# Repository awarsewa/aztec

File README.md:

# aztec
Bringing a 1976 pinball machine back to life.

[:corn: Wiki](https://github.com/awarsewa/aztec/wiki)

### The machine
Aztec is a Williams® pinball machine for 4 players. Check it out on the [Internet Pinball Machine Database](https://www.ipdb.org/machine.cgi?gid=119). There is also a [solid state version](https://www.ipdb.org/machine.cgi?gid=4828) of the same machine. Mine is from the electromechanical series -- and this is where the fun starts. Of course it wasn't functional. The entire cabinet had been completely gutted, with only a few tilt mechanisms left dangling about. However, the playfield and the backbox were still mostly intact. Repairing it seemed tough, but since it's cool to have your own pinball machine, I decided to give it a shot.

### The project
It would have been rather expensive and difficult to get original spare parts for, or replicas of, all the missing components. So why not replace aztec's brain with a microcontroller? The looks and feel of the machine would still be the same. Only what's under the hood would be slightly more modern. Maybe this is a sacrilege for real pinball lovers... I have a feeling it is. Like an inverse Frankenstein - pretty on the outside. But I already did it, so there's no way back and no repentance. If you want to know how I've done it, check out the [:corn: repository wiki](https://github.com/awarsewa/aztec/wiki).

### What's in this repository?
The source code running on the microcontroller and the PCB schematics. Basically everything you need to do something similar. 

### Getting involved
In case you have questions or suggestions, need support or simply want to get in touch, feel free to [send me a message](mailto:alexander.warsewa@posteo.net?subject=[Aztec]).

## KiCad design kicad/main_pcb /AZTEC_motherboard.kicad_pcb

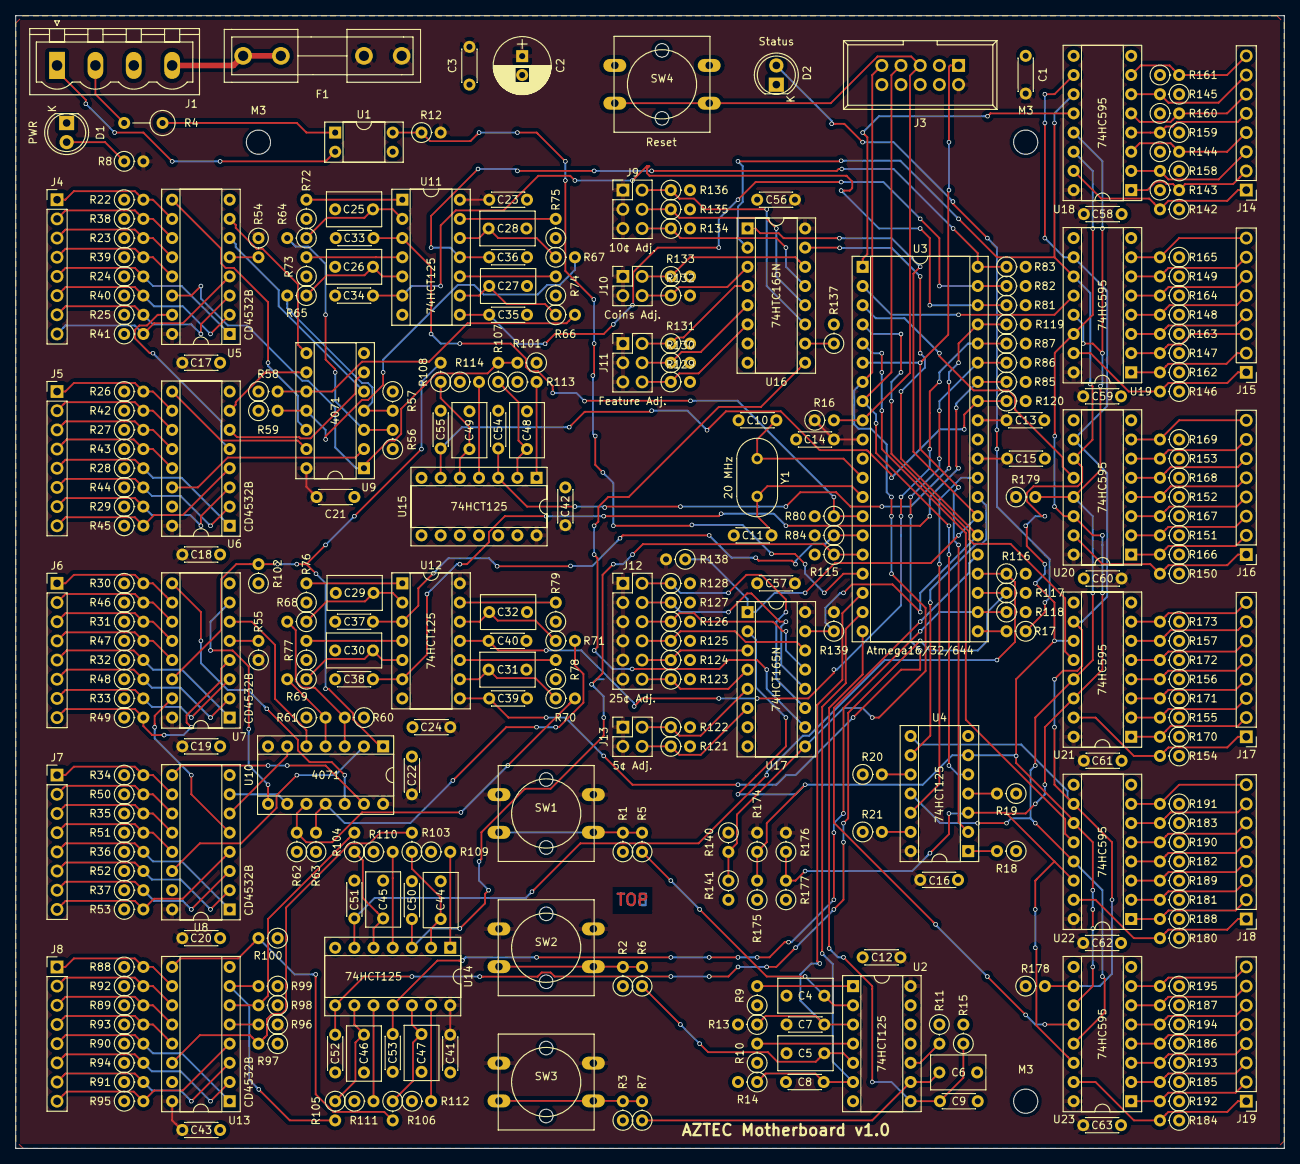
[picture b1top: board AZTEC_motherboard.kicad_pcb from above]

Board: 2 copper layers, 168.0 x 150.0 mm, 310 parts (0 on the bottom side), 227 nets.

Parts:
C1, C3, C7, C8, C9, C12, C13, C14, C15, C16, C17, C18, C19, C20, C21, C22, C23, C24, C33, C34, C35, C36, C37, C38, C39, C40, C41, C42, C43, C50, C51, C52, C53, C54, C55, C56, C57, C58, C59, C60, C61, C62, C63: 100n; C_Disc_D4.3mm_W1.9mm_P5.00mm
C2: 1u; CP_Radial_D7.5mm_P2.50mm
C4, C5, C6, C25, C26, C27, C28, C29, C30, C31, C32, C44, C45, C46, C47, C48, C49: 1µ; C_Rect_L7.2mm_W4.5mm_P5.00mm_FKS2_FKP2_MKS2_MKP2
C10, C11: 22p; C_Disc_D4.3mm_W1.9mm_P5.00mm
D1: PWR; LED-5MM
D2: STATUS; LED-5MM
F1: Fuse; Fuseholder5x20_horiz_open_inline_Type-I
J1: Conn_01x04_Female; PhoenixContact_MSTBVA-G_04x5.08mm_Vertical
J3: ISP; IDC_Header_Straight_10pins
J4: Inputs_1; Pin_Header_Straight_1x08_Pitch2.54mm
J5: Inputs_2; Pin_Header_Straight_1x08_Pitch2.54mm
J6: Inputs_3; Pin_Header_Straight_1x08_Pitch2.54mm
J7: Inputs_4; Pin_Header_Straight_1x08_Pitch2.54mm
J8: Inputs_5; Pin_Header_Straight_1x08_Pitch2.54mm
J9: 10¢ Adjust; Pin_Header_Straight_2x03_Pitch2.54mm
J10: 2 coins - 3 plays; Pin_Header_Straight_2x02_Pitch2.54mm
J11: Feature Adjust; Pin_Header_Straight_2x03_Pitch2.54mm
J12: 25¢ Adjust; Pin_Header_Straight_2x06_Pitch2.54mm
J13: 5¢ Adjust; Pin_Header_Straight_2x02_Pitch2.54mm
J14: Outputs_1; Pin_Header_Straight_1x08_Pitch2.54mm
J15: Outputs_2; Pin_Header_Straight_1x08_Pitch2.54mm
J16: Outputs_3; Pin_Header_Straight_1x08_Pitch2.54mm
J17: Outputs_4; Pin_Header_Straight_1x08_Pitch2.54mm
J18: Outputs_5; Pin_Header_Straight_1x08_Pitch2.54mm
J19: Outputs_6; Pin_Header_Straight_1x08_Pitch2.54mm
M3, M3#2, M3#3: MountingHole_3.2mm_M3
R1, R2, R3, R9, R10, R11, R12, R13, R14, R15, R16, R18, R19, R20, R21, R22, R23, R24, R25, R26, R27, R28, R29, R30, R31, R32, R33, R34, R35, R36, R37, R38, R39, R40, R41, R42, R43, R44, R45, R46, R47, R48, R49, R50, R51, R52, R53, R54, R55, R56, R57, R58, R59, R60, R61, R62, R63, R72, R73, R74, R75, R76, R77, R78, R79, R80, R81, R82, R83, R84, R85, R86, R87, R88, R89, R90, R91, R92, R93, R94, R95, R96, R97, R98, R99, R100, R101, R102, R109, R110, R111, R112, R113, R114, R115, R116, R117, R118, R119, R120, R121, R122, R123, R124, R125, R126, R127, R128, R129, R130, R131, R132, R133, R134, R135, R136, R137, R138, R139, R140, R141, R142, R143, R144, R145, R146, R147, R148, R149, R150, R151, R152, R153, R154, R155, R156, R157, R158, R159, R160, R161, R162, R163, R164, R165, R166, R167, R168, R169, R170, R171, R172, R173, R174, R175, R176, R177, R178, R179, R180, R181, R182, R183, R184, R185, R186, R187, R188, R189, R190, R191, R192, R193, R194, R195: 10k; R_Axial_DIN0207_L6.3mm_D2.5mm_P2.54mm_Vertical
R4: 2k2; R_Axial_DIN0309_L9.0mm_D3.2mm_P5.08mm_Vertical
R5, R6, R7, R64, R65, R66, R67, R68, R69, R70, R71, R103, R104, R105, R106, R107, R108: 22k; R_Axial_DIN0207_L6.3mm_D2.5mm_P2.54mm_Vertical
R8, R17: 100R; R_Axial_DIN0207_L6.3mm_D2.5mm_P2.54mm_Vertical
SW1, SW2, SW3, SW4: Reset; SW_PUSH-AZTEC
U1: SFH620A; DIP-4_W7.62mm_Socket
U2, U4, U11, U12, U14, U15: 74HCT125; DIP-14_W7.62mm_Socket
U3: ATMEGA16/32/644; DIP-40_W15.24mm_Socket
U5, U6, U7, U8, U13: CD4532B; DIP-16_W7.62mm_Socket
U9, U10: 4071; DIP-14_W7.62mm_Socket
U16, U17: 74HCT165N; DIP-16_W7.62mm_Socket
U18, U19, U20, U21, U22, U23: 74HC595; DIP-16_W7.62mm_Socket
Y1: 20 MHz; Resonator-2pin_w10.0mm_h5.0mm

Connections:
/AC_zero_crossing: R12.1, U1.4, U3.17
/Adjusts/CP: R174.1, R175.2, U4.6, U16.2, U17.2, U18.11, U19.11, U20.11, U21.11, U22.11, U23.11
/Adjusts/~CE: R139.1, U3.26, U16.15, U17.15
/Adjusts/~PL: R138.1, U3.27, U16.1, U17.1
/Button1: C7.2, R13.1, U2.3, U3.18
/Button2: C8.2, R14.1, U2.6, U3.19
/Button3: C9.2, R15.1, U2.8, U3.20
/Inputs/GS1: C33.2, R80.1, U3.14, U11.3
/Inputs/GS2: C37.2, R84.1, U3.15, U12.3
/Inputs/GS3: C50.2, R115.1, U3.16, U14.3
/Inputs/Q10: C36.2, R83.1, U3.40, U11.11
/Inputs/Q11: C35.2, R82.1, U3.39, U11.8
/Inputs/Q12: C34.2, R81.1, U3.38, U11.6
/Inputs/Q13: C54.2, R119.1, U3.37, U15.3
/Inputs/Q20: C40.2, R87.1, U3.36, U12.11
/Inputs/Q21: C39.2, R86.1, U3.35, U12.8
/Inputs/Q22: C38.2, R85.1, U3.34, U12.6
/Inputs/Q23: C55.2, R120.1, U3.33, U15.6
/Inputs/Q30: C53.2, R118.1, U3.22, U14.11
/Inputs/Q31: C52.2, R117.1, U3.23, U14.8
/Inputs/Q32: C51.2, R116.1, U3.24, U14.6
/MISO: J3.9, R140.2, R141.1, U3.7, U17.9
/MOSI: J3.1, U3.6, U4.2
/Outputs/MOSI_buf: R176.1, R177.2, U4.3, U18.14, U19.14, U20.14, U21.14, U22.14, U23.14
/Outputs/RCK1: U3.1, U18.12
/Outputs/RCK2: U3.2, U19.12
/Outputs/RCK3: U3.3, U20.12
/Outputs/RCK4: U3.4, U21.12
/Outputs/RCK5: U3.5, U22.12
/Outputs/RCK6: U3.25, U23.12
/Outputs/~OE_buf: R179.2, U4.11, U18.13, U19.13, U20.13, U21.13, U22.13, U23.13
/Outputs/~SCL_buf: R178.2, U4.8, U18.10, U19.10, U20.10, U21.10, U22.10, U23.10
/SCK: J3.7, U3.8, U4.5
/~OE: U3.29, U4.12
/~RESET: J3.5, R16.2, SW4.2, SW4.4, U3.9
/~SCL: U3.28, U4.9
GND: C1.1, C2.2, C3.1, C4.1, C5.1, C6.1, C7.1, C8.1, C9.1, C10.2, C11.2, C12.2, C13.1, C14.1, C15.2, C16.2, C17.1, C18.1, C19.1, C20.1, C21.1, C22.1, C23.2, C24.2, C25.1, C26.1, C27.1, C28.1, C29.1, C30.1, C31.1, C32.1, C33.1, C34.1, C35.1, C36.1, C37.1, C38.1, C39.1, C40.1, C41.2, C42.2, C43.1, C44.1, C45.1, C46.1, C47.1, C48.1, C49.1, C50.1, C51.1, C52.1, C53.1, C54.1, C55.1, C56.1, C57.1, C58.2, C59.2, C60.2, C61.2, C62.2, C63.2, D1.1, D2.1, J1.3, J3.4, J3.6, J3.8, J3.10, R1.1, R2.1, R3.1, R9.1, R10.1, R11.1, R13.2, R14.2, R15.2, R18.1, R19.1, R20.1, R21.1, R22.1, R23.1, R24.1, R25.1, R26.1, R27.1, R28.1, R29.1, R30.1, R31.1, R32.1, R33.1, R34.1, R35.1, R36.1, R37.1, R38.1, R39.1, R40.1, R41.1, R42.1, R43.1, R44.1, R45.1, R46.1, R47.1, R48.1, R49.1, R50.1, R51.1, R52.1, R53.1, R56.1, R57.1, R58.1, R59.1, R60.1, R61.1, R62.1, R63.1, R72.1, R73.1, R74.1, R75.1, R76.1, R77.1, R78.1, R79.1, R80.2, R81.2, R82.2, R83.2, R84.2, R85.2, R86.2, R87.2, R88.1, R89.1, R90.1, R91.1, R92.1, R93.1, R94.1, R95.1, R97.1, R98.1, R99.1, R100.1, R101.1, R102.1, R109.1, R110.1, R111.1, R112.1, R113.1, R114.1, R115.2, R116.2, R117.2, R118.2, R119.2, R120.2, R121.2, R122.2, R123.2, R124.2, R125.2, R126.2, R127.2, R128.2, R129.2, R130.2, R131.2, R132.2, R133.2, R134.2, R135.2, R136.2, R137.2, R141.2, R142.1, R143.1, R144.1, R145.1, R146.1, R147.1, R148.1, R149.1, R150.1, R151.1, R152.1, R153.1, R154.1, R155.1, R156.1, R157.1, R158.1, R159.1, R160.1, R161.1, R162.1, R163.1, R164.1, R165.1, R166.1, R167.1, R168.1, R169.1, R170.1, R171.1, R172.1, R173.1, R175.1, R177.1, R180.1, R181.1, R182.1, R183.1, R184.1, R185.1, R186.1, R187.1, R188.1, R189.1, R190.1, R191.1, R192.1, R193.1, R194.1, R195.1, SW4.1, SW4.3, U1.3, U2.7, U3.11, U3.31, U4.7, U5.8, U6.8, U7.8, U8.8, U9.7, U10.7, U11.7, U12.7, U13.8, U14.7, U15.7, U16.8, U17.8, U18.8, U19.8, U20.8, U21.8, U22.8, U23.8
unnamed: C4.2, R5.1, U2.2
unnamed: C5.2, R6.1, U2.5
unnamed: C6.2, R7.1, U2.9
unnamed: C10.1, U3.12, Y1.1
unnamed: C11.1, U3.13, Y1.2
unnamed: C25.2, R64.1, U11.2
unnamed: C26.2, R65.1, U11.5
unnamed: C27.2, R66.1, U11.9
unnamed: C28.2, R67.1, U11.12
unnamed: C29.2, R68.1, U12.2
unnamed: C30.2, R69.1, U12.5
unnamed: C31.2, R70.1, U12.9
unnamed: C32.2, R71.1, U12.12
unnamed: C44.2, R103.1, U14.2
unnamed: C45.2, R104.1, U14.5
unnamed: C46.2, R105.1, U14.9
unnamed: C47.2, R106.1, U14.12
unnamed: C48.2, R107.1, U15.2
unnamed: C49.2, R108.1, U15.5
unnamed: D1.2, R8.1
unnamed: D2.2, R17.1
unnamed: F1.2, J1.4
unnamed: J1.1, U1.2
unnamed: J1.2, R4.2
unnamed: J4.1, R22.2, U5.10
unnamed: J4.2, R38.2, U5.11
unnamed: J4.3, R23.2, U5.12
unnamed: J4.4, R39.2, U5.13
unnamed: J4.5, R24.2, U5.1
unnamed: J4.6, R40.2, U5.2
unnamed: J4.7, R25.2, U5.3
unnamed: J4.8, R41.2, U5.4
unnamed: J5.1, R26.2, U6.10
unnamed: J5.2, R42.2, U6.11
unnamed: J5.3, R27.2, U6.12
unnamed: J5.4, R43.2, U6.13
unnamed: J5.5, R28.2, U6.1
unnamed: J5.6, R44.2, U6.2
unnamed: J5.7, R29.2, U6.3
unnamed: J5.8, R45.2, U6.4
unnamed: J6.1, R30.2, U7.10
unnamed: J6.2, R46.2, U7.11
unnamed: J6.3, R31.2, U7.12
unnamed: J6.4, R47.2, U7.13
unnamed: J6.5, R32.2, U7.1
unnamed: J6.6, R48.2, U7.2
unnamed: J6.7, R33.2, U7.3
unnamed: J6.8, R49.2, U7.4
unnamed: J7.1, R34.2, U8.10
unnamed: J7.2, R50.2, U8.11
unnamed: J7.3, R35.2, U8.12
unnamed: J7.4, R51.2, U8.13
unnamed: J7.5, R36.2, U8.1
unnamed: J7.6, R52.2, U8.2
unnamed: J7.7, R37.2, U8.3
unnamed: J7.8, R53.2, U8.4
unnamed: J8.1, R88.2, U13.10
unnamed: J8.2, R92.2, U13.11
unnamed: J8.3, R89.2, U13.12
unnamed: J8.4, R93.2, U13.13
unnamed: J8.5, R90.2, U13.1
unnamed: J8.6, R94.2, U13.2
unnamed: J8.7, R91.2, U13.3
unnamed: J8.8, R95.2, U13.4
unnamed: J9.2, R136.1, U16.11
unnamed: J9.4, R135.1, U16.12
unnamed: J9.6, R134.1, U16.13
unnamed: J10.2, R133.1, U16.14
unnamed: J10.4, R132.1, U16.3
unnamed: J11.2, R131.1, U16.4
unnamed: J11.4, R130.1, U16.5
unnamed: J11.6, R129.1, U16.6
unnamed: J12.2, R128.1, U17.11
unnamed: J12.4, R127.1, U17.12
unnamed: J12.6, R126.1, U17.13
unnamed: J12.8, R125.1, U17.14
unnamed: J12.10, R124.1, U17.3
unnamed: J12.12, R123.1, U17.4
unnamed: J13.2, R122.1, U17.5
unnamed: J13.4, R121.1, U17.6
unnamed: J14.1, R142.2, U18.15
unnamed: J14.2, R158.2, U18.1
unnamed: J14.3, R143.2, U18.2
unnamed: J14.4, R159.2, U18.3
unnamed: J14.5, R144.2, U18.4
unnamed: J14.6, R160.2, U18.5
unnamed: J14.7, R145.2, U18.6
unnamed: J14.8, R161.2, U18.7
unnamed: J15.1, R146.2, U19.15
unnamed: J15.2, R162.2, U19.1
unnamed: J15.3, R147.2, U19.2
unnamed: J15.4, R163.2, U19.3
unnamed: J15.5, R148.2, U19.4
unnamed: J15.6, R164.2, U19.5
unnamed: J15.7, R149.2, U19.6
unnamed: J15.8, R165.2, U19.7
unnamed: J16.1, R150.2, U20.15
unnamed: J16.2, R166.2, U20.1
unnamed: J16.3, R151.2, U20.2
unnamed: J16.4, R167.2, U20.3
unnamed: J16.5, R152.2, U20.4
unnamed: J16.6, R168.2, U20.5
unnamed: J16.7, R153.2, U20.6
unnamed: J16.8, R169.2, U20.7
unnamed: J17.1, R154.2, U21.15
unnamed: J17.2, R170.2, U21.1
unnamed: J17.3, R155.2, U21.2
unnamed: J17.4, R171.2, U21.3
unnamed: J17.5, R156.2, U21.4
unnamed: J17.6, R172.2, U21.5
unnamed: J17.7, R157.2, U21.6
unnamed: J17.8, R173.2, U21.7
unnamed: J18.1, R180.2, U22.15
unnamed: J18.2, R188.2, U22.1
unnamed: J18.3, R181.2, U22.2
unnamed: J18.4, R189.2, U22.3
unnamed: J18.5, R182.2, U22.4
unnamed: J18.6, R190.2, U22.5
unnamed: J18.7, R183.2, U22.6
unnamed: J18.8, R191.2, U22.7
unnamed: J19.1, R184.2, U23.15
unnamed: J19.2, R192.2, U23.1
unnamed: J19.3, R185.2, U23.2
unnamed: J19.4, R193.2, U23.3
unnamed: J19.5, R186.2, U23.4
unnamed: J19.6, R194.2, U23.5
unnamed: J19.7, R187.2, U23.6
unnamed: J19.8, R195.2, U23.7
unnamed: R1.2, R5.2, SW1.2, SW1.4
unnamed: R2.2, R6.2, SW2.2, SW2.4
unnamed: R3.2, R7.2, SW3.2, SW3.4
unnamed: R4.1, U1.1
unnamed: R9.2, U2.1
unnamed: R10.2, U2.4
unnamed: R11.2, U2.10
unnamed: R17.2, U3.21
unnamed: R18.2, U4.1
unnamed: R19.2, U4.4
unnamed: R20.2, U4.10
unnamed: R21.2, U4.13
unnamed: R54.2, U5.5
unnamed: R55.2, U7.5
unnamed: R56.2, R64.2, U9.3
unnamed: R57.2, R65.2, U9.4
unnamed: R58.2, R66.2, U9.10
unnamed: R59.2, R67.2, U9.11
unnamed: R60.2, R68.2, U10.3
unnamed: R61.2, R69.2, U10.4
unnamed: R62.2, R70.2, U10.10
unnamed: R63.2, R71.2, U10.11
unnamed: R72.2, U11.1
unnamed: R73.2, U11.4
unnamed: R74.2, U11.10
unnamed: R75.2, U11.13
unnamed: R76.2, U12.1
unnamed: R77.2, U12.4
unnamed: R78.2, U12.10
unnamed: R79.2, U12.13
unnamed: R96.2, U13.5
unnamed: R100.2, R106.2, U13.9
unnamed: R101.2, R107.2, U5.14, U9.1
unnamed: R102.2, R108.2, U7.14, U10.1
unnamed: R97.2, R103.2, U13.14
unnamed: R98.2, R104.2, U13.6
unnamed: R99.2, R105.2, U13.7
unnamed: R109.2, U14.1
unnamed: R110.2, U14.4
unnamed: R111.2, U14.10
unnamed: R112.2, U14.13
unnamed: R113.2, U15.1
unnamed: R114.2, U15.4
unnamed: R137.1, U16.10
unnamed: U5.6, U9.5
unnamed: U5.7, U9.8
unnamed: U5.9, U9.12
unnamed: U5.15, U6.5
unnamed: U6.6, U9.6
unnamed: U6.7, U9.9
unnamed: U6.9, U9.13
unnamed: U6.14, U9.2
unnamed: U7.15, U8.5
unnamed: U8.14, U10.2
unnamed: U7.6, U10.5
unnamed: U8.6, U10.6
unnamed: U7.7, U10.8
unnamed: U8.7, U10.9
unnamed: U7.9, U10.12
unnamed: U8.9, U10.13
unnamed: U16.9, U17.10
VCC: C1.2, C2.1, C3.2, C12.1, C13.2, C14.2, C15.1, C16.1, C17.2, C18.2, C19.2, C20.2, C21.2, C22.2, C23.1, C24.1, C41.1, C42.1, C43.2, C56.2, C57.2, C58.1, C59.1, C60.1, C61.1, C62.1, C63.1, F1.1, J3.2, J9.1, J9.3, J9.5, J10.1, J10.3, J11.1, J11.3, J11.5, J12.1, J12.3, J12.5, J12.7, J12.9, J12.11, J13.1, J13.3, R8.2, R12.2, R16.1, R54.1, R55.1, R96.1, R138.2, R139.2, R140.1, R174.2, R176.2, R178.1, R179.1, SW1.1, SW1.3, SW2.1, SW2.3, SW3.1, SW3.3, U2.14, U3.10, U3.30, U3.32, U4.14, U5.16, U6.16, U7.16, U8.16, U9.14, U10.14, U11.14, U12.14, U13.16, U14.14, U15.14, U16.16, U17.16, U18.16, U19.16, U20.16, U21.16, U22.16, U23.16

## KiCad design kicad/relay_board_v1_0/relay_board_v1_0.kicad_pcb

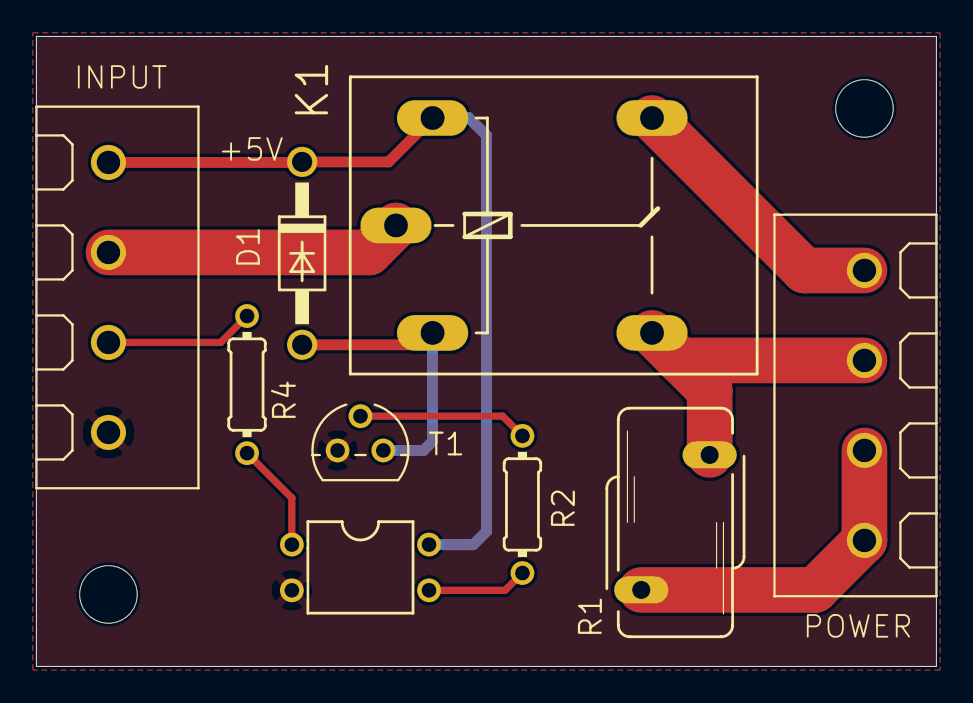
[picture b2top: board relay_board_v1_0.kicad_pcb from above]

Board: 2 copper layers, 50.0 x 35.0 mm, 11 parts (0 on the bottom side), 11 nets.

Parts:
@HOLE0, @HOLE1: (no value)
D1: 1N4007; DO41-10
INPUT: OSTTA040161; 040161
K1: G5LE
OK1: TLP621; DIL04
POWER: OSTTA040161; 040161
R1: 10D470K
R2: 1k2; 0204_7
R4: 270; 0204_7
T1: 2N3904; TO92

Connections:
+5V: D1.C, INPUT.1, K1.2, OK1.4
GND: INPUT.4, OK1.2, T1.3
unnamed: D1.A, K1.1, T1.1
unnamed: INPUT.2, K1.P
unnamed: INPUT.3, R4.2
unnamed: K1.O, POWER.4
unnamed: K1.S, POWER.3, R1.2
unnamed: OK1.1, R4.1
unnamed: OK1.3, R2.2
unnamed: POWER.1, POWER.2, R1.1
unnamed: R2.1, T1.2

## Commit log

2021-01-26 added source code
2021-01-26 added brains schematic
2021-01-26 added relays board
2021-01-27 Set theme jekyll-theme-cayman
2021-01-27 Set theme jekyll-theme-hacker
2021-02-04 cleaned up source code; removed recursion-free routines
2021-02-04 deleted pages website
2021-02-05 image for wiki
2021-02-05 added pcb rendering
2021-02-05 annotated PCB rendering
2021-02-06 added image of schematic symbols
2021-02-07 added image of Z relay
2021-02-10 added picture of ball count unit
2021-02-10 added score motor image
2021-02-12 added images of relay board
2021-02-12 changed image of relay pcb schematic
2021-02-12 added picture of power supply
2021-02-13 added image of my machine
2021-02-13 exchanged Eagle PCB with KiCAD version
2021-02-13 deleted old PCB versions
2021-02-13 igonre .ipynb*
